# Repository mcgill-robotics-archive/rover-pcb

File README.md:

# science-dev
Science board

# Big Update (10/05/2021)
The board has a linear regulator to power the Peltier cooler + CCD sensor assembly. 
Started initializing PWM signals needed for CCD Sensor

# Big Update (06/05/2021)
The board now powers (currently three) LED strips to light up the
inside of the science module.

It also powers a solenoid used by soil collection.

# Big Update (18/03/2021)
There is now an onboard relay switching power to the entire board.

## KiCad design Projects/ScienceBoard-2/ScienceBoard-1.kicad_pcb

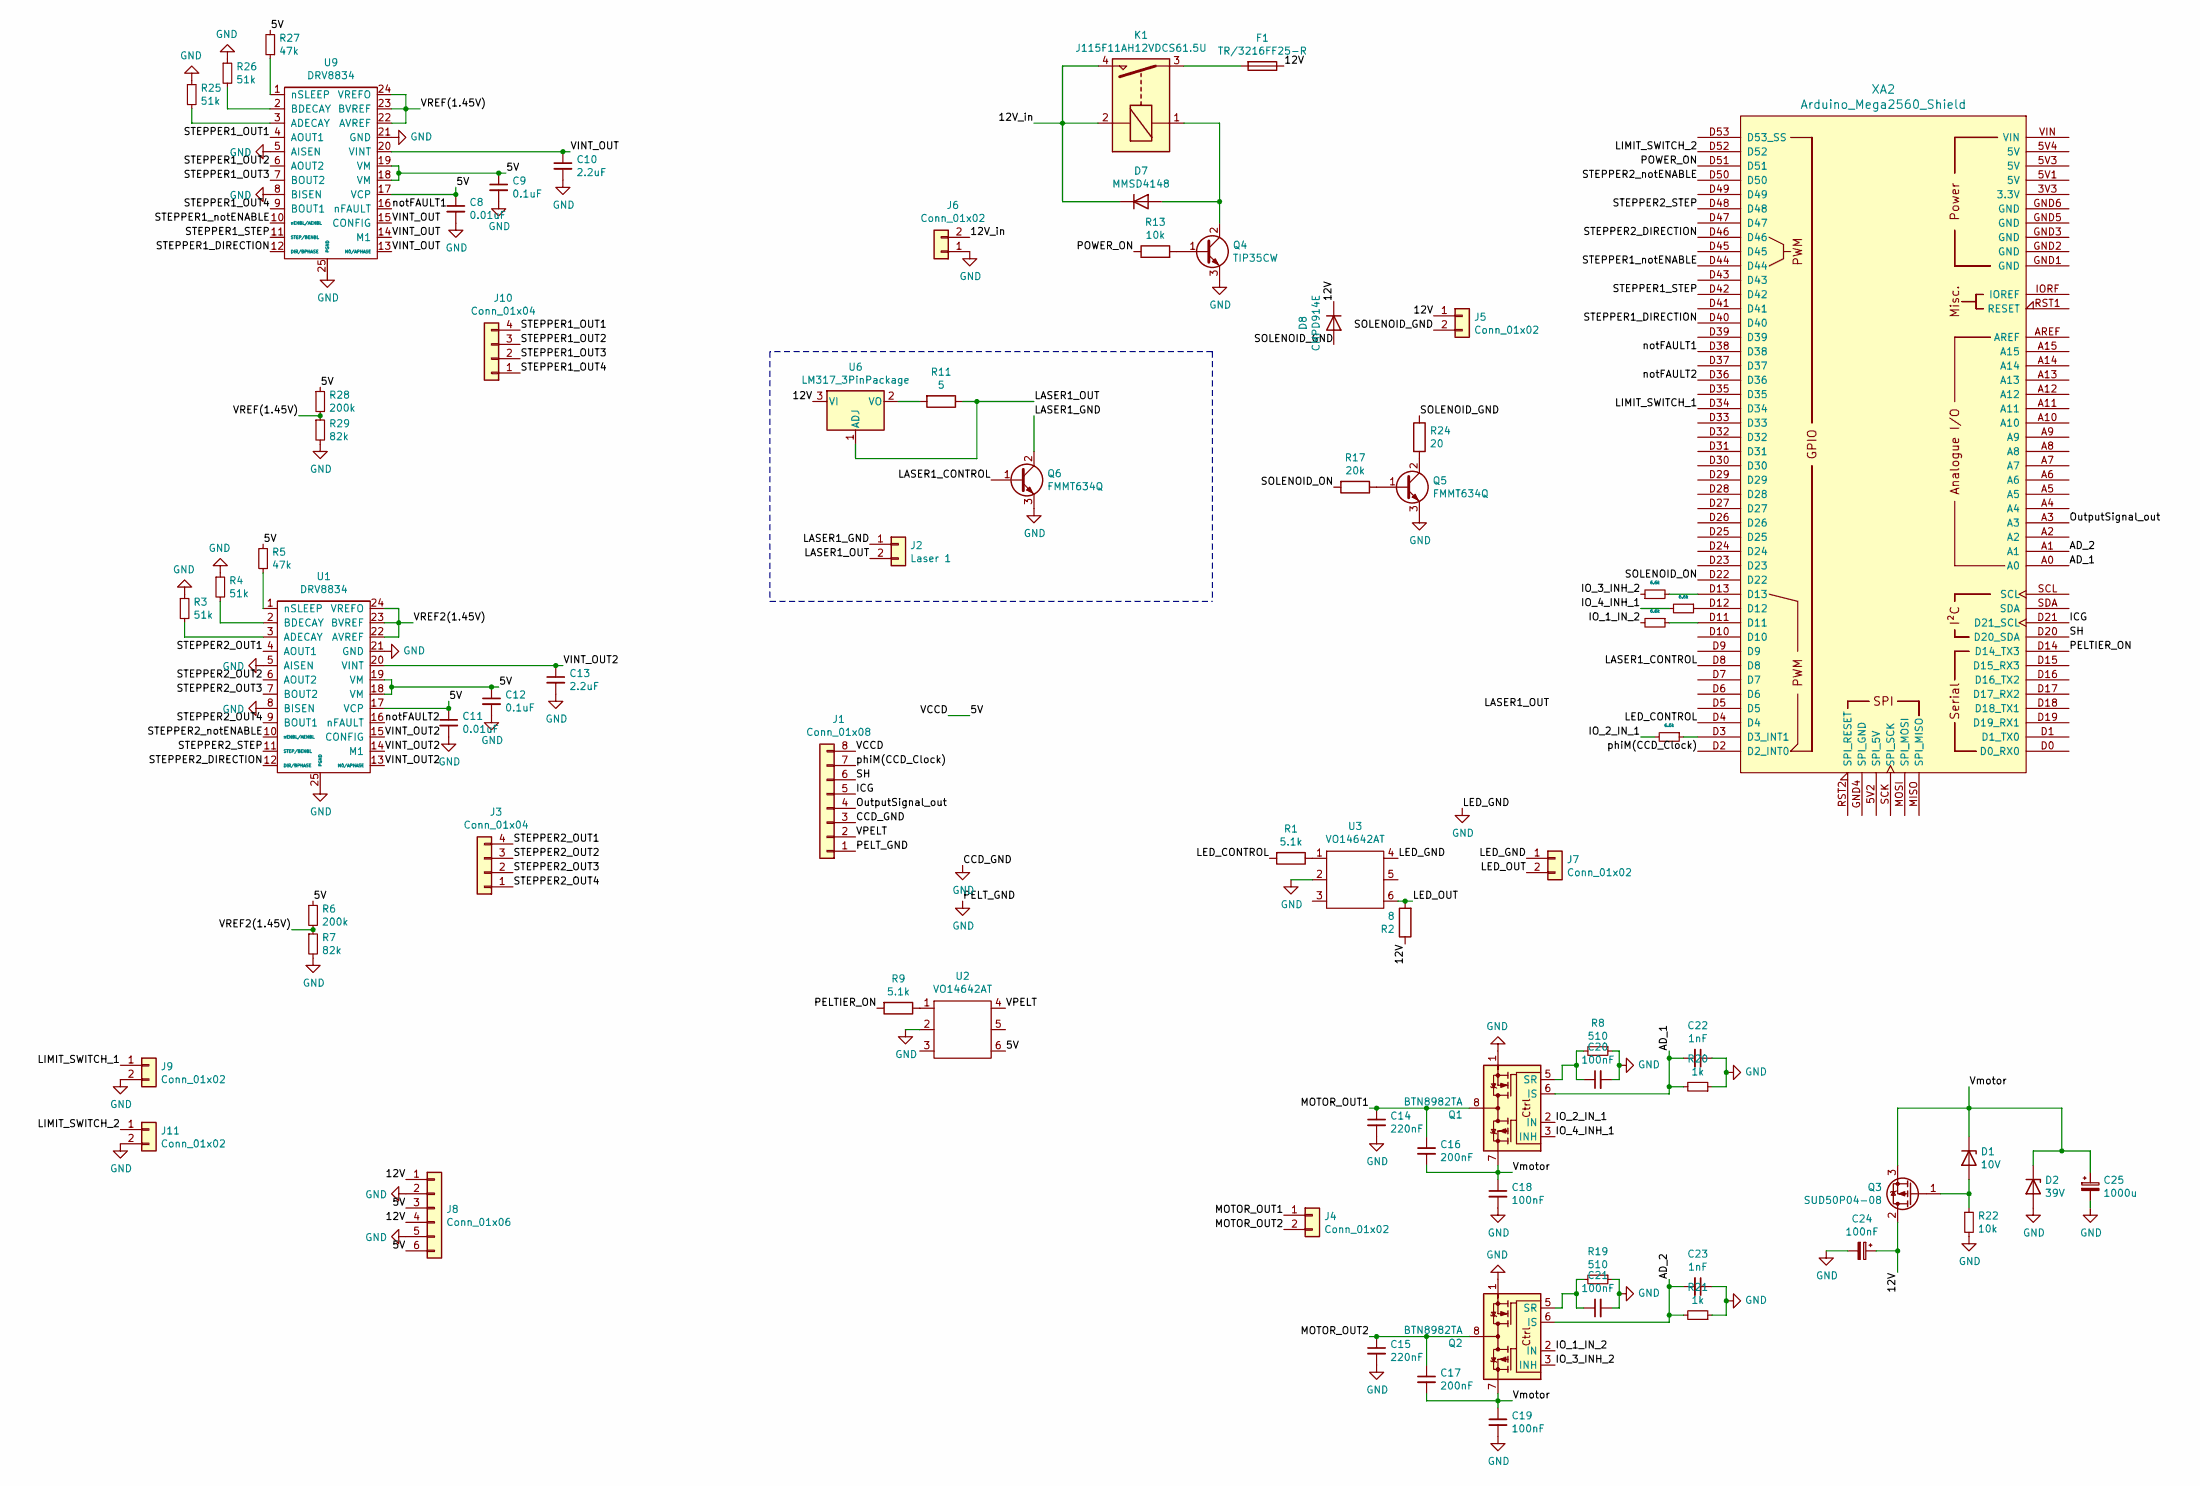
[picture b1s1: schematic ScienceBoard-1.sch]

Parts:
C8, C11: 0.01uF; C_0402_1005Metric
C9, C12: 0.1uF; C_0402_1005Metric
C10, C13: 2.2uF; C_0402_1005Metric
C14, C15: 220nF; C_0402_1005Metric
C16, C17: 200nF; C_0402_1005Metric
C18, C19, C20, C21: 100nF; C_0402_1005Metric
C22, C23: 1nF; C_0402_1005Metric
C24: 100nF; C_Elec_6.3x7.7
C25: 1000u; C_Radial_D10.0mm_H16.0mm_P5.00mm
D1: 10V; D_SOD-123F
D2: 39V; D_SOD-123FL
D7: MMSD4148; D_SOD-123
D8: CMPD914E; SOT-23
F1: TR/3216FF25-R; Fuse_1206_3216Metric
J1: Conn_01x08; Molex_KK-254_AE-6410-08A_1x08_P2.54mm_Vertical
J2: Laser 1; CUI_MJ1-2533-SMT
J3, J10: Conn_01x04; Molex_KK-254_AE-6410-04A_1x04_P2.54mm_Vertical
J4, J5, J7, J9, J11: Conn_01x02; Molex_KK-254_AE-6410-02A_1x02_P2.54mm_Vertical
J6: Conn_01x02; Molex_Mega-Fit_76829-0002_2x01_P5.70mm_Vertical
J8: Conn_01x06; Molex_Micro-Fit_3.0_43045-0612_2x03_P3.00mm_Vertical
K1: J115F11AH12VDCS61.5U; Relay_StandexMeder_UMS
Q1, Q2: BTN8982TA; TO-263-7_TabPin8
Q3: SUD50P04-08; TO-252-2
Q4: TIP35CW; TO-247-3_Vertical
Q5, Q6: FMMT634Q; SOT-23
R1, R9: 5.1k; R_0402_1005Metric
R2: 8; R_0402_1005Metric
R3, R4, R25, R26: 51k; R_0402_1005Metric
R5, R27: 47k; R_0402_1005Metric
R6, R28: 200k; R_0402_1005Metric
R7, R29: 82k; R_0402_1005Metric
R8, R19: 510; R_0402_1005Metric
R11: 5; R_0402_1005Metric
R13, R22: 10k; R_0402_1005Metric
R17: 20k; R_0402_1005Metric
R20, R21: 1k; R_0402_1005Metric
R24: 20; R_0402_1005Metric
R31, R32, R33, R34: 6.6k; R_0402_1005Metric
U1, U9: DRV8834; HTSSOP-24-1EP_4.4x7.8mm_P0.65mm_EP3.2x5mm
U2, U3: VO14642AT
U6: LM317_3PinPackage; SOT-223-3_TabPin2
XA2: Arduino_Mega2560_Shield

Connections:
/5V: C8.1, C9.1, C11.1, C12.1, J1.8, J8.3, J8.6, R5.2, R6.1, R27.2, R28.1, U1.17 (VCP), U1.18 (VM), U1.19 (VM), U2.6, U9.17 (VCP), U9.18 (VM), U9.19 (VM)
/12V: C24.1, D8.1 (K), F1.1, J5.1, J8.1, J8.4, Q3.2 (D), R2.1, U6.3 (VI)
/12V_in: D7.1 (K), J6.2, K1.2, K1.4
/AD_1: C22.2, Q1.6 (IS), R20.2, XA2.A0
/AD_2: C23.2, Q2.6 (IS), R21.2, XA2.A1
/ICG: J1.5, XA2.D21 (D21_SCL)
/IO_1_IN_2: Q2.2 (IN), R32.2
/IO_2_IN_1: Q1.2 (IN), R33.2
/IO_3_INH_2: Q2.3 (INH), R31.1
/IO_4_INH_1: Q1.3 (INH), R34.2
/LASER1_CONTROL: Q6.1 (B), XA2.D8
/LASER1_GND: J2.1, Q6.2 (C)
/LASER1_OUT: J2.2, R11.1, U6.1 (ADJ)
/LED_CONTROL: R1.2, XA2.D4
/LED_OUT: J7.2, R2.2, U3.6
/LIMIT_SWITCH_1: J9.1, XA2.D34
/LIMIT_SWITCH_2: J11.1, XA2.D52
/MOTOR_OUT1: C14.1, C16.1, J4.1, Q1.4, Q1.8
/MOTOR_OUT2: C15.1, C17.1, J4.2, Q2.4, Q2.8
/OutputSignal_out: J1.4, XA2.A3
/PELTIER_ON: R9.2, XA2.D14 (D14_TX3)
/POWER_ON: R13.1, XA2.D51
/SH: J1.6, XA2.D20 (D20_SDA)
/SOLENOID_GND: D8.2 (A), J5.2, R24.1
/SOLENOID_ON: R17.2, XA2.D22
/STEPPER1_DIRECTION: U9.12 (DIR/BPHASE), XA2.D40
/STEPPER1_OUT1: J10.4, U9.4 (AOUT1)
/STEPPER1_OUT2: J10.3, U9.6 (AOUT2)
/STEPPER1_OUT3: J10.2, U9.7 (BOUT2)
/STEPPER1_OUT4: J10.1, U9.9 (BOUT1)
/STEPPER1_STEP: U9.11 (STEP/BENBL), XA2.D42
/STEPPER1_notENABLE: U9.10 (nENBL/AENBL), XA2.D44
/STEPPER2_DIRECTION: U1.12 (DIR/BPHASE), XA2.D46
/STEPPER2_OUT1: J3.4, U1.4 (AOUT1)
/STEPPER2_OUT2: J3.3, U1.6 (AOUT2)
/STEPPER2_OUT3: J3.2, U1.7 (BOUT2)
/STEPPER2_OUT4: J3.1, U1.9 (BOUT1)
/STEPPER2_STEP: U1.11 (STEP/BENBL), XA2.D48
/STEPPER2_notENABLE: U1.10 (nENBL/AENBL), XA2.D50
/VINT_OUT: C10.1, U9.13 (M0/APHASE), U9.14 (M1), U9.15 (CONFIG), U9.20 (VINT)
/VINT_OUT2: C13.1, U1.13 (M0/APHASE), U1.14 (M1), U1.15 (CONFIG), U1.20 (VINT)
/VPELT: J1.2, U2.4
/VREF2(1.45V): R6.2, R7.1, U1.22 (AVREF), U1.23 (BVREF), U1.24 (VREFO)
/VREF(1.45V): R28.2, R29.1, U9.22 (AVREF), U9.23 (BVREF), U9.24 (VREFO)
/Vmotor: C16.2, C17.2, C18.1, C19.1, C25.1, D1.1 (K), D2.1 (K), Q1.7, Q2.7, Q3.3 (S)
/notFAULT1: U9.16 (nFAULT), XA2.D38
/notFAULT2: U1.16 (nFAULT), XA2.D36
/phiM(CCD_Clock): J1.7, XA2.D2 (D2_INT0)
GND: C8.2, C9.2, C10.2, C11.2, C12.2, C13.2, C14.2, C15.2, C18.2, C19.2, C20.2, C21.2, C22.1, C23.1, C24.2, C25.2, D2.2 (A), J1.1, J1.3, J6.1, J7.1, J8.2, J8.5, J9.2, J11.2, Q1.1, Q2.1, Q4.3 (E), Q5.3 (E), Q6.3 (E), R3.1, R4.1, R7.2, R8.1, R19.1, R20.1, R21.1, R22.2, R25.1, R26.1, R29.2, U1.5 (AISEN), U1.8 (BISEN), U1.21 (GND), U1.25 (PGND), U2.2, U3.2, U3.4, U9.5 (AISEN), U9.8 (BISEN), U9.21 (GND), U9.25 (PGND)
unnamed: C20.1, Q1.5 (SR), R8.2
unnamed: C21.1, Q2.5 (SR), R19.2
unnamed: D1.2 (A), Q3.1 (G), R22.1
unnamed: D7.2 (A), K1.1, Q4.2 (C)
unnamed: F1.2, K1.3
unnamed: Q4.1 (B), R13.2
unnamed: Q5.1 (B), R17.1
unnamed: Q5.2 (C), R24.2
unnamed: R1.1, U3.1
unnamed: R3.2, U1.3 (ADECAY)
unnamed: R4.2, U1.2 (BDECAY)
unnamed: R5.1, U1.1 (nSLEEP)
unnamed: R9.1, U2.1
unnamed: R11.2, U6.2 (VO)
unnamed: R25.2, U9.3 (ADECAY)
unnamed: R26.2, U9.2 (BDECAY)
unnamed: R27.1, U9.1 (nSLEEP)
unnamed: R31.2, XA2.D13
unnamed: R32.1, XA2.D11
unnamed: R33.1, XA2.D3 (D3_INT1)
unnamed: R34.1, XA2.D12

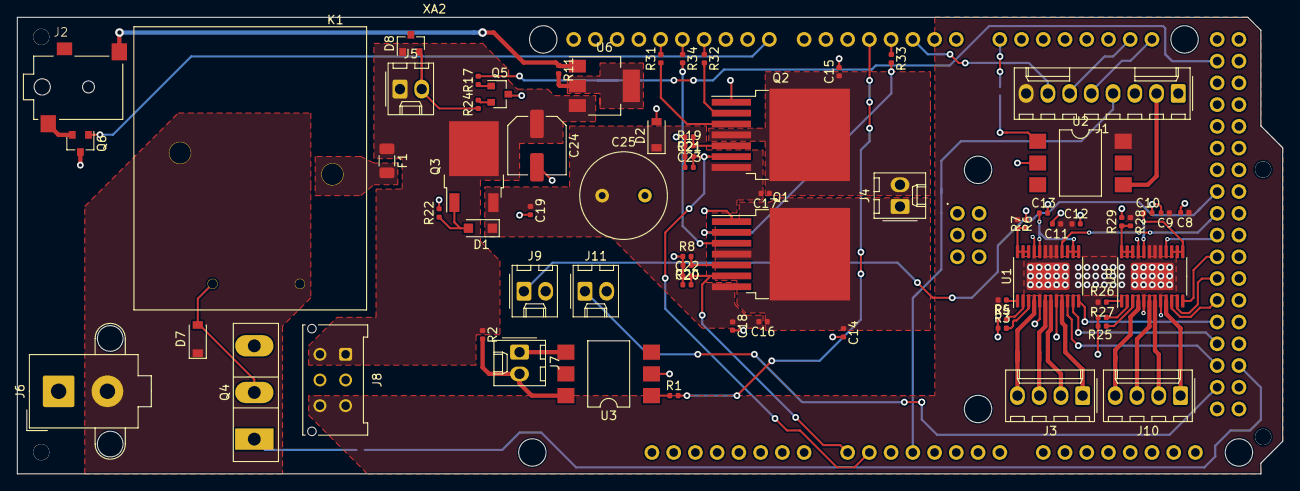
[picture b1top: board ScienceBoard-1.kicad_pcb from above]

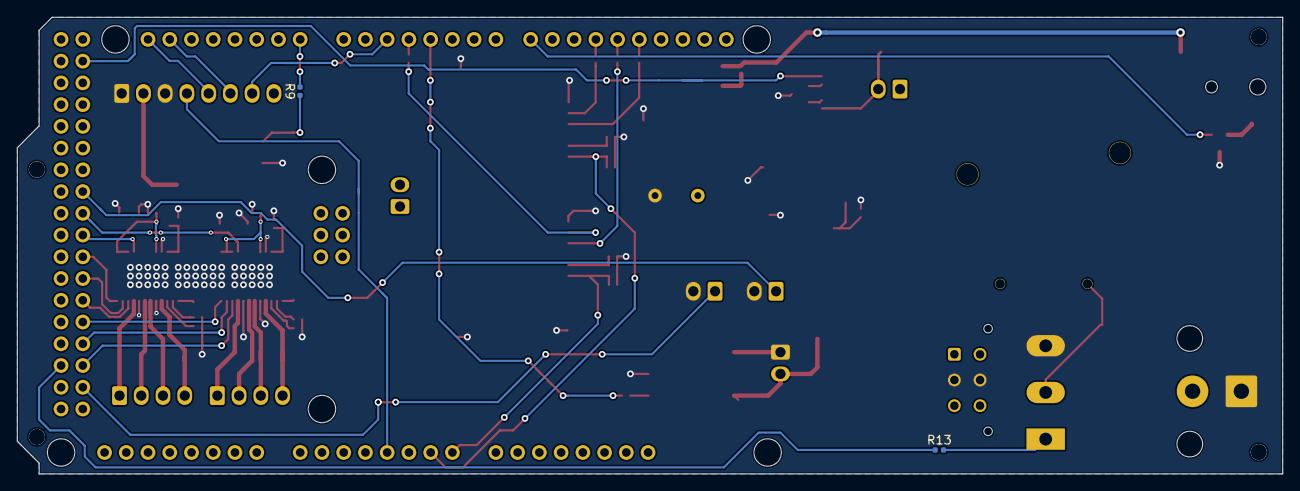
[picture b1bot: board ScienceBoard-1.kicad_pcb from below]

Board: 4 copper layers, 147.8 x 53.3 mm, 73 parts (2 on the bottom side), 70 nets.

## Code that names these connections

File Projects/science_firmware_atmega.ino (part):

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 * 
 * D38 - notFAULT1: High when Stepper #1 is not in a fault condition
 * D36 - notFAULT2: High when Stepper #2 is not in a fault condition
 * D44 - STEPPER1_notENABLE: Stepper #1 is enabled when this pin is low.
 * D50 - STEPPER2_notENABLE: Stepper #2 is enabled when this pin is low.
 * 
 * ----[Stepper Control Lines]----
 * D42 - STEPPER1_STEP: Stepper #1 will advance one step on the rising edge of this pin.
 * D40 - STEPPER1_DIRECTION: Stepper #1 will change direction on the rising edge of this pin.
 * D48 - STEPPER2_STEP: Stepper #2 will advance one step on the rising edge of this pin.
 * D46 - STEPPER2_DIRECTION: Stepper #2 will change direction on the rising edge of this pin.
 * 
 * ----[Limit Switches]----
 * D34 - LIMIT_SWITCH_1
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 * A1 - AD_2
 * 
 * ----[Laser]----
 * D8 - LASER1_CONTROL: Laser is on when this pin is high
 * 
 * ----[LED's]----
 * D4 - LED_CONTROL: LED's are on when this pin is high
 * 
 * ----[Solenoid]----
 * D22 - SOLENOID_ON: Solenoid is on when this pin is high
 * 
 * ----[CCD Sensor]----
 * TODO: Figure out how the sensor works
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#include <SPI.h>
#include <IfxMotorControlShield.h>

const int POWER_ON = 51;
const int LIMIT_SWITCH_1 = 34;
const int LIMIT_SWITCH_2 = 52;
const int notFAULT1 = 38;
const int notFAULT2 = 36;
const int STEPPER1_notENABLE = 44;
const int STEPPER2_notENABLE = 50;
const int STEPPER1_STEP = 42;
const int STEPPER1_DIRECTION = 40;
const int STEPPER2_STEP = 48;
const int STEPPER2_DIRECTION = 46;
const int IN_1 = 3;
const int IN_2 = 11;
const int INH_1 = 12;
const int INH_2 = 13;
const int LASER1_CONTROL = 8;
const int CCD_Clock = 2;
const int SH = 20;
const int ICG = 21;
const int SOLENOID_ON = 22;
const int LED_CONTROL = 4;
const int PELTIER_ON = 14;

#define AD_1 A0
#define AD_2 A1

// CCD sensor defines
#define OutputSignal_out A3
#define CCD_CLOCK_PERIOD 50 // hundredth of usecs (1e-8 secs)
#define CCD_CLOCK_DUTY_CYCLE 5 // 100 msecs in hundredth of usecs (1e-8 secs)

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#define ICG_DUTY_CYCLE 50

#define MCLK 0x10
#define ICG 0x01
#define SH  0x02
#define PIXELS 3691
#define MIN_SIGNAL 10
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
void setup() {
  // TODO: Look into CCD pins and figure out whether they are outputs or inputs
  pinMode(POWER_ON, OUTPUT);
  pinMode(SOLENOID_ON, OUTPUT);
  pinMode(LED_CONTROL, OUTPUT);
  pinMode(STEPPER1_notENABLE, OUTPUT);
  pinMode(STEPPER2_notENABLE, OUTPUT);
  pinMode(STEPPER1_STEP, OUTPUT);
  pinMode(STEPPER1_DIRECTION, OUTPUT);
  pinMode(STEPPER2_STEP, OUTPUT);
  pinMode(STEPPER2_DIRECTION, OUTPUT);
  pinMode(LASER1_CONTROL, OUTPUT);
  pinMode(OutputSignal_out, INPUT);
  pinMode(AD_1, INPUT);
  pinMode(AD_2, INPUT);
  pinMode(IN_1, OUTPUT);
  pinMode(IN_2, OUTPUT);
  pinMode(INH_1, OUTPUT);
  pinMode(INH_2, OUTPUT);
  pinMode(CCD_Clock, OUTPUT);
  pinMode(SH, OUTPUT);
  pinMode(ICG, OUTPUT);
  pinMode(LIMIT_SWITCH_1, INPUT);
  pinMode(LIMIT_SWITCH_2, INPUT);

  // TODO: Communications setup (UART, I2C, SPI)
  Serial.begin(UART_BAUD_RATE);
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  while(!(notFAULT1 and notFAULT2)){}           // Wait until both stepper IC's start up properly

  //Attach interrupts to their ISR's (Interrupt Service Routines):
  attachInterrupt(digitalPinToInterrupt(notFAULT1), stepperonefault_ISR, LOW);
  attachInterrupt(digitalPinToInterrupt(notFAULT2), steppertwofault_ISR, LOW);
  //(ISR's are at the bottom)

  // Initialize brushless DC motor controller.
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
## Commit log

2020-07-11 Add TM4C123GH6PMI schematic
2020-09-26 added power pcb project
2020-09-26 light modification
2020-09-26 +files
2020-10-02 added missing components to pcb file
2020-10-03 changed board size
2020-10-03 Changed the size of resistors and capacitors
2020-10-03 modif
2020-10-06 Pcb layout done
2020-10-07 routed everything except tm4c
2020-10-07 only tm4c left
2020-10-07 started routing tm4c
2020-10-08 only 4 pins left on tm4c
2020-10-09 finished rough draft for powerboard bcb
2020-10-09 some test commit
2020-10-09 added fuse to relayB
2020-10-09 new fuse
2020-10-09 R22 removed
2020-10-10 Add files via upload
    PCB and Schematic for Drive
2020-10-10 Fixed intial branch of the schmatic
2020-10-11 Uploaded version 1 of the arm board
    3 BDC motor board
2020-10-11 added 2 more layers
2020-10-11 increased board dimensions to 12x18cm
2020-10-11 added planes for 24V and GND
2020-10-11 rearranged components for better routing
2020-10-11 more rearrangements
2020-10-12 Changed resistors on relay_A
2020-10-12 Changed resistors on both branches, Pins and new routing is left todo
2020-10-12 Pins and routing left to do
2020-10-12 did some top layer routing
2020-10-12 Added some vias to ground
2020-10-13 Majority of routing done
2020-10-17 Renamed & reorganized pcb files
2020-10-17 Edits to PCB
    Changed board size, added DRV8874-Q1
2020-10-22 removed green text and tried to make the board smaller
2020-10-24 Path changes
    renamed ambiguously named libraries
2020-10-24 tried to add a 6pin connector. this boi is too thick
2020-10-31 moved the connectors to the edge of the board and moved taller components to topside of the board
    Note: Sam is the best
2020-11-03 Test
    Just an example
2020-11-03 Added libraries
    for the driver and transciever
2020-11-03 Test
    Testing libraries
2020-11-03 Uploading V2
    New project meant to implement the 4 layer PCB
2020-11-06 4 Layers + Limit Switches
2020-11-07 Uploaded new board designs
2020-11-07 Added ground plane connections
2020-11-07 updated ground plane changes
2020-11-08 Changes to Sch and Pcb
    -Changed limit switch connection from NC & GND to NO & GND in Sch + Pcb
    -Changed 24V polygon on power layer and 24V GND polygon on GND layer to direct connect
    -Fixed unconnected GNDs
    -Split the GND layer polygons into two (24V and 3.3V/5V)
    -Changed 3.3V/5V trace widths to 20 mil
    -Changed 24V trace widths to 30 mil
2020-11-14 Changed Min Track Width
    + General cleaning up
2020-11-21 added first connector
2020-11-27 Changed trace widths
    For the motor outputs
2020-11-28 Initial commit
    Added pizza
2020-11-28 Science Board Schematic
    First iteration of a schematic for the science board.
2020-11-28 Science Board kicad
    Schematic for the first iteration of the science board.
2021-01-02 Uploaded new drive PCB board with brakes
2021-01-09 Updated the files for Drive PCB
2021-01-10 Jan 9 Changes
    -Adjusted driver output track widths (some concern regarding pad-to-pad clearances, but the output tracks need to be wide)
    -Reduced the number of thermal relief pads to 3/driver, and reduced hole diameter
    -Rerouted tracks to avoid them overlapping the middle of the motor drivers
    -Imported and updated schematics to include the chosen power and limit switch connectors
2021-01-10 changes before working on planes
2021-01-10 preliminary routing done
2021-01-17 Added and placed limit switch + power connectors
    had to move around some other components to fit them
2021-01-18 Updated Final Design of the Drive PCB
2021-02-03 little fixes with the planes/tracks and made the connectors flush with the board
2021-02-13 leaving to a new branch
2021-02-13 Added Connectors
    Swapped out the placeholder connectors for the motor outputs and encoder for spec'd molex connectors
2021-02-13 Added connector libraries
    For the motor output and encoder molex connectors
2021-02-17 Description
    Description and pinout for the science board
2021-02-27 Updated the final design of the drive pcb
    Removed redundant, traces, updated the plane definitions, and updated the power connector based on the board current requirements.
2021-02-27 trying to fix samac lib problem
2021-02-28 Science Board Firmware
    The sketch that controls the board
2021-03-08 redid routing from scratch
2021-03-08 more work on routing
2021-03-08 Finished routing
2021-03-08 Added Vias to PWR Plane
2021-03-13 Create Version 6
    Updated PCB with new connectors
2021-03-13 Updated PCB with finalized connectors
2021-03-13 Final Update of PCB
2021-03-18 Create science_easy_edit
2021-03-18 Update science_easy_edit
2021-03-18 Rename science_easy_edit to science_desc_easyedit
2021-03-20 Updated Final PCB by adding 2 limit switches
2021-03-20 Updated PCB by adding 2 addition limit switches
2021-03-20 Final Drive PCB
2021-03-25 added the molex limit switch connector to pcb and sch lib
2021-03-25 fixes
2021-03-26 Updated PCB with correct Limit Switch Connector
2021-03-26 Updated PCB Schematics
    Imported correct Limit Switch Connectors
2021-03-26 Final PCB Schematics
2021-03-27 made changes
2021-03-27 implementing alex's fizes
2021-03-27 done tweaking
2021-03-29 Updated PCB Changed Limit Switch Connector
2021-04-03 added non-generic fuses
2021-04-03 added drive connector
2021-04-10 Final Changes Made to PCB
2021-04-11 General Changes
    Resized vias, now smaller in diameter
    Adjusting X1 position
    Changed GND width 20mil --> 15mil
    Rerouted VCORE, IPROPI_A
    General houskeeping, cleaning up traces
2021-05-06 Add files via upload
    Add controls for solenoid and LED's
2021-05-08 Committing unfinished spi_config
2021-05-08 test file
    Just for testing the a pull request
2021-05-08 Updated PCB with Final Improvements
2021-05-09 Moved C14-C17 next to the 3.3V on each side of the TM4C
2021-05-11 Began Setting Up PWM Signals for CCD
2021-05-12 Deleted old way to set up CCD clock
2021-05-15 Create science_firmware_atmega
2021-05-15 Rename science_firmware_atmega to science_firmware_atmega.ino
2021-05-15 Init Pin Clocks, Timer Frequency, Read Function
2021-05-15 Changed active low pins to active high
    We don't have active low output pins anymore after the last board revision, aside from STEPPER1_notENABLE and STEPPER2_notENABLE
2021-05-15 fixed capacitor positions
2021-05-15 Stepper code updates
    Fixed the minimum angle per step, added "go to specified angle" functionality as discussed in science module meeting
2021-05-15 Deleted old functions
    Deleted old delay functions + duplicate init for serial
2021-05-19 Fixed SPI, JLS pins and 24V plane
2021-05-22 added new fuses
2021-05-23 Switched Encoder Pins
    From GPIO's to SSI_TX/RX's
2021-05-23 Updated Encoder Pins
    Switched CLK_A/B to SSI0/1_CLK pins
2021-05-25 Outdated
    New link: https://github.com/mcgill-robotics/rover-embedded/tree/EP56_science_system_firmware
2021-05-29 finished antenna board schematic (preliminary)
2021-05-29 finished routing for preliminary design
2021-05-30 Made changes to the schematic / pcb, fixed errors, cleaned it up
2021-05-30 Updated Encoders
2021-06-06 before paul changes
2021-06-06 after paul changes
2021-06-06 clean up
2021-06-06 released output files
2021-06-12 Updated SC Connectors
2021-06-15 Updated Power Connector
2021-06-16 before the storm
2021-06-16 after the storm
2021-06-18 pcb doc ready for release
2021-06-19 Removed DRV8874's
    Replaced with connectors meant to interface with the Cytron MD10C Controller
2021-06-20 Updated Linear Regulator
2021-10-30 Create BLDC Board Resources
2021-10-30 Created board assembly resources
